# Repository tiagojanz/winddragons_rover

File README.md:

# WindDragons - Sistema de Telemetria e Controlo Náutico (Base & Rover)

Projeto de automação e telemetria para boias robóticas náuticas autónomas (**Rovers**) e estação de controlo com ecrã (**Base Station**), baseado na **arquitetura universal Dual ESP32-C6** (Master Lafvin LCD 1.47" + Coprocessador DevKitC-1).

---

## 🛰️ Arquitetura do Sistema (Dual ESP32-C6 em Ambos os Nós)

```
[ WindDragons Portal (Cloud) ]
        ▲
        │ HTTPS REST API (JSON)
        ▼
┌────────────────────────────────────────────────────────┐
│ BASE STATION (Dual ESP32-C6)                           │
│  - Master Lafvin: LCD 1.47" IPS, MicroSD, Web/WiFi,   │
│                   Joystick PS5 e Coordenador OTA Dual │
│         ▲                                              │
│         │ UART Inter-ESP (921600 baud)                │
│         ▼                                              │
│  - Coprocessador C6: Rádio LoRa SX1278 (433MHz)       │
└──────────────────────────┬─────────────────────────────┘
                           │
                           │ LoRa 433 MHz (Ra-02 / SX1278)
                           ▼
┌────────────────────────────────────────────────────────┐
│ ROVER (Boia Náutica - Dual ESP32-C6)                   │
│  - Master Lafvin: LCD 1.47" IPS, MicroSD, Web/WiFi,   │
│                   Joystick local e Coordenador OTA    │
│         ▲                                              │
│         │ UART Inter-ESP (921600 baud)                │
│         ▼                                              │
│  - Coprocessador C6: LoRa 433MHz, GPS LC29H, PWM     │
│    (Motor, Leme, Guincho, Trinco) e Sensores          │
└────────────────────────────────────────────────────────┘
```

---

## 🔌 Esquema de Barramentos e Conexões

O módulo **LoRa Ra-02 (SX1278 a 433MHz)** é ligado exclusivamente ao **Coprocessador ESP32-C6** (evitando conflito com o barramento SPI partilhado entre o LCD e o MicroSD do Lafvin):

### Módulo LoRa SX1278 (433MHz) — Coprocessador ESP32-C6 DevKitC
| Pino Ra-02 | Pino ESP32-C6 | Notas |
| :--- | :--- | :--- |
| **VCC** | `3.3V` | Barramento independente 3.3V_C6 |
| **GND** | `GND` | Terra comum de referência |
| **SCK** | `GPIO 5` | Hardware SPI SCLK |
| **MOSI**| `GPIO 7` | Hardware SPI MOSI |
| **MISO**| `GPIO 4` | Hardware SPI MISO |
| **NSS / CS** | `GPIO 6` | Hardware SPI CS do LoRa |
| **DIO0**| `GPIO 0` | Interrupção de receção de pacotes |

---

### Slot MicroSD (TF Card Onboard) — Em ambas as placas
O slot MicroSD está integrado diretamente na placa ESP32-C6-LCD-1.47 e partilha o barramento SPI com o ecrã ST7789:
| Função SD | Pino ESP32-C6 | Notas |
| :--- | :--- | :--- |
| **CS** | `IO4` | Chip Select do Cartão SD (Ativo LOW) |
| **MOSI** | `IO6` | Partilhado com LCD MOSI |
| **SCLK** | `IO7` | Partilhado com LCD SCLK |
| **MISO** | `IO5` | Linha de leitura MISO |

**Ficheiros suportados na raiz do cartão:**
- `/config.txt` — Ficheiro de configurações lido automaticamente no boot.
- `/waypoints.txt` — Ficheiro de coordenadas de navegação (lido no Rover).
- `/telemetry.csv` — Registo automático de telemetria (GPS, velocidade, rumo, bateria e estado do motor).

---

### Build 1: ROVER (A Boia)
| Componente | Pino do Módulo / Atuador | Pino ESP32-C6 | Função |
| :--- | :--- | :--- | :--- |
| **Motor (ESC)** | Sinal PWM | `IO0` | 50Hz PWM (1000µs a 2000µs, centro 1500µs) |
| **Servo do Leme** | Sinal PWM | `IO1` | 50Hz PWM (Ângulo de direção) |
| **Guincho Âncora** | Sinal PWM | `IO23` | Servo de rotação contínua (1500µs parado, <1500 desce, >1500 sobe) |
| **GPS Quectel LC29H** | TX do GPS | `IO19` | RX UART1 (115200 bps) |
| | RX do GPS | `IO18` | TX UART1 |
| | VCC / GND | `3.3V / GND` | Alimentação |
| **LED RGB Onboard** | Integrado | `IO8` | Estado: Verde (GPS OK), Azul (LoRa), Vermelho (Failsafe) |

---

### Build 2: BASE (Comando Remoto com Ecrã)
| Componente | Pino do Módulo | Pino ESP32-C6 | Função |
| :--- | :--- | :--- | :--- |
| **Joystick (4 vias)** | VCC | `3.3V` | Alimentação do joystick |
| | GND | `GND` | Terra |
| | VRx (Avanço/Recuo) | `IO0` | Entrada Analógica ADC1_CH0 (Aceleração) |
| | VRy (Direção) | `IO1` | Entrada Analógica ADC1_CH1 (Leme) |
| **Botões de Âncora** | Subir Âncora | `IO18` | Entrada Digital (Pull-up interno) |
| | Descer Âncora | `IO19` | Entrada Digital (Pull-up interno) |
| **Botão BOOT** | Onboard | `IO9` | Cicla páginas de ecrã (Comando -> Frota -> Rede) |
| **Ecrã LCD 1.47"** | Integrado ST7789 | `IO14, 15, 21, 22` | Dashboard multi-ecrã Landscape 320x172 (Comando, Frota de Rovers e Rede WiFi) |

---

## 🌐 Conectividade WiFi, Modo AP & Servidor Web

A Base Station inclui gestão inteligente de ligações WiFi e um Servidor Web HTTP responsivo:

### 1. Arranque Inteligente e Fallback para Modo AP:
- **No arranque**: a Base tenta ligar-se à rede marcada como **Padrão (Default)** ou às redes secundárias guardadas na memória NVS (timeout de 8s).
- **Se não houver ligação**: entra automaticamente em **Modo Ponto de Acesso (AP)**:
  - **SSID do AP**: `WindDragons-Base`
  - **Password**: `12345678`
  - **Endereço IP**: `http://192.168.4.1`
- **Ecrã LCD**: ao arrancar (e no menu através de `7. INFO REDE / IP`):
  - Se ligado a WiFi: apresenta o **endereço IP** atribuído (`http://192.168.x.x`), SSID e sinal RSSI.
  - Se em modo AP: apresenta o **SSID da Base**, a password e o endereço `http://192.168.4.1`.

### 2. Páginas do Servidor HTTP:
- **Em Modo AP**:
  - `/wifi`: Interface para procurar redes próximas (Scan WiFi), adicionar redes e marcar a rede de casa/porto como **Default**.
- **Em Modo WiFi (Cliente)**:
  - `/wifi`: Gestão de múltiplas redes guardadas, alteração da rede default, remoção e scanner de sinal.
  - `/gps`: Telemetria e coordenadas GPS do Rover ativo, rumo da proa, velocidade em nós e links diretos para Google Maps e OpenStreetMap.
  - `/battery`: Monitorização da bateria LiPo 4S (tensão do pack, média por célula, percentagem colorida e estado de saúde).
  - `/control`: Comando remoto da boia via rádio LoRa (acelerador do motor ESC com presets, leme, âncora, cremalheira, hold station e botão de paragem de emergência).

---

## 🚀 Como Compilar e Enviar o Firmware

Com o **PlatformIO** instalado:

### 1. Compilar e Enviar para o Rover:
O Rover possui dois módulos ESP32-C6:
- **Rover C6 (Slave):** Controla Rádio LoRa, GPS LC29H, ESC do Motor, Servos e Sensores.
- **Rover Lafvin (Master):** Controla o Ecrã LCD 1.47" ST7789, Leitor MicroSD e Joystick.

```bash
# Rover C6 (Slave - LoRa / GPS / Atuadores)
pio run -e rover_c6 -t upload
pio device monitor -e rover_c6

# Rover Lafvin (Master - LCD / MicroSD)
pio run -e rover_lafvin -t upload
pio device monitor -e rover_lafvin

# Ou gerar pacote unificado para atualização remota (OTA):
python3 scripts/bundle_firmware.py
```

### 2. Compilar e Enviar para a Base:
```bash
# Compilar e Enviar Base
pio run -e base -t upload

# Monitor Série (115200 baud)
pio device monitor -e base
```

---

## 📡 Integração com a API WindDragons

A cada 3 segundos, a Base agrupa os rovers ativos e envia um pedido `POST` para `https://winddragons.app/api/circuits/station/telemetry`:

```json
{
  "station_id": "BASE-ALCOCHETE-01",
  "rovers": [
    {
      "rover_code": "ROVER-01",
      "lat": 38.750508,
      "lng": -8.973995,
      "speed": 0.2,
      "heading": 185.0,
      "battery_pct": 92,
      "battery_voltage": 12.5,
      "motor_status": "holding_station",
      "anchor_status": "retracted",
      "anchor_depth_m": 0.0,
      "rssi": -65
    }
  ]
}
```

Caso o servidor responda com comandos pendentes (ex: `DROP_ANCHOR`, `RETRACT_ANCHOR`, `HOLD_STATION`), a Base coloca o comando na fila e transmite-o imediatamente via rádio LoRa para o rover visado!

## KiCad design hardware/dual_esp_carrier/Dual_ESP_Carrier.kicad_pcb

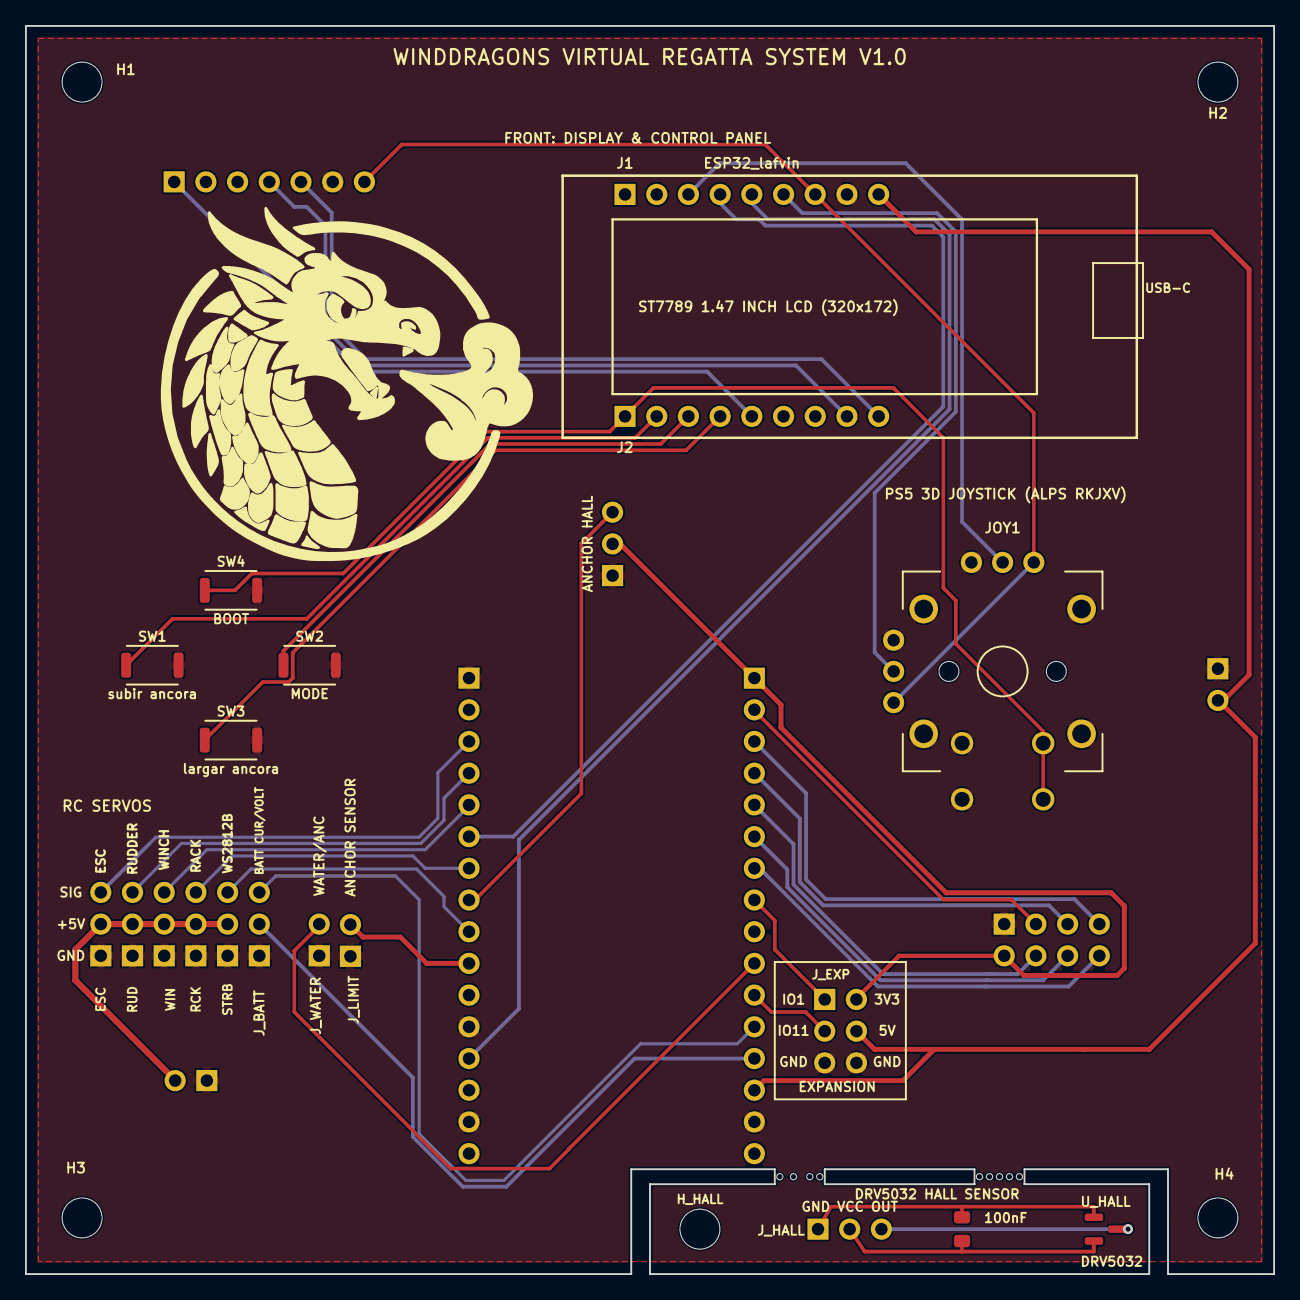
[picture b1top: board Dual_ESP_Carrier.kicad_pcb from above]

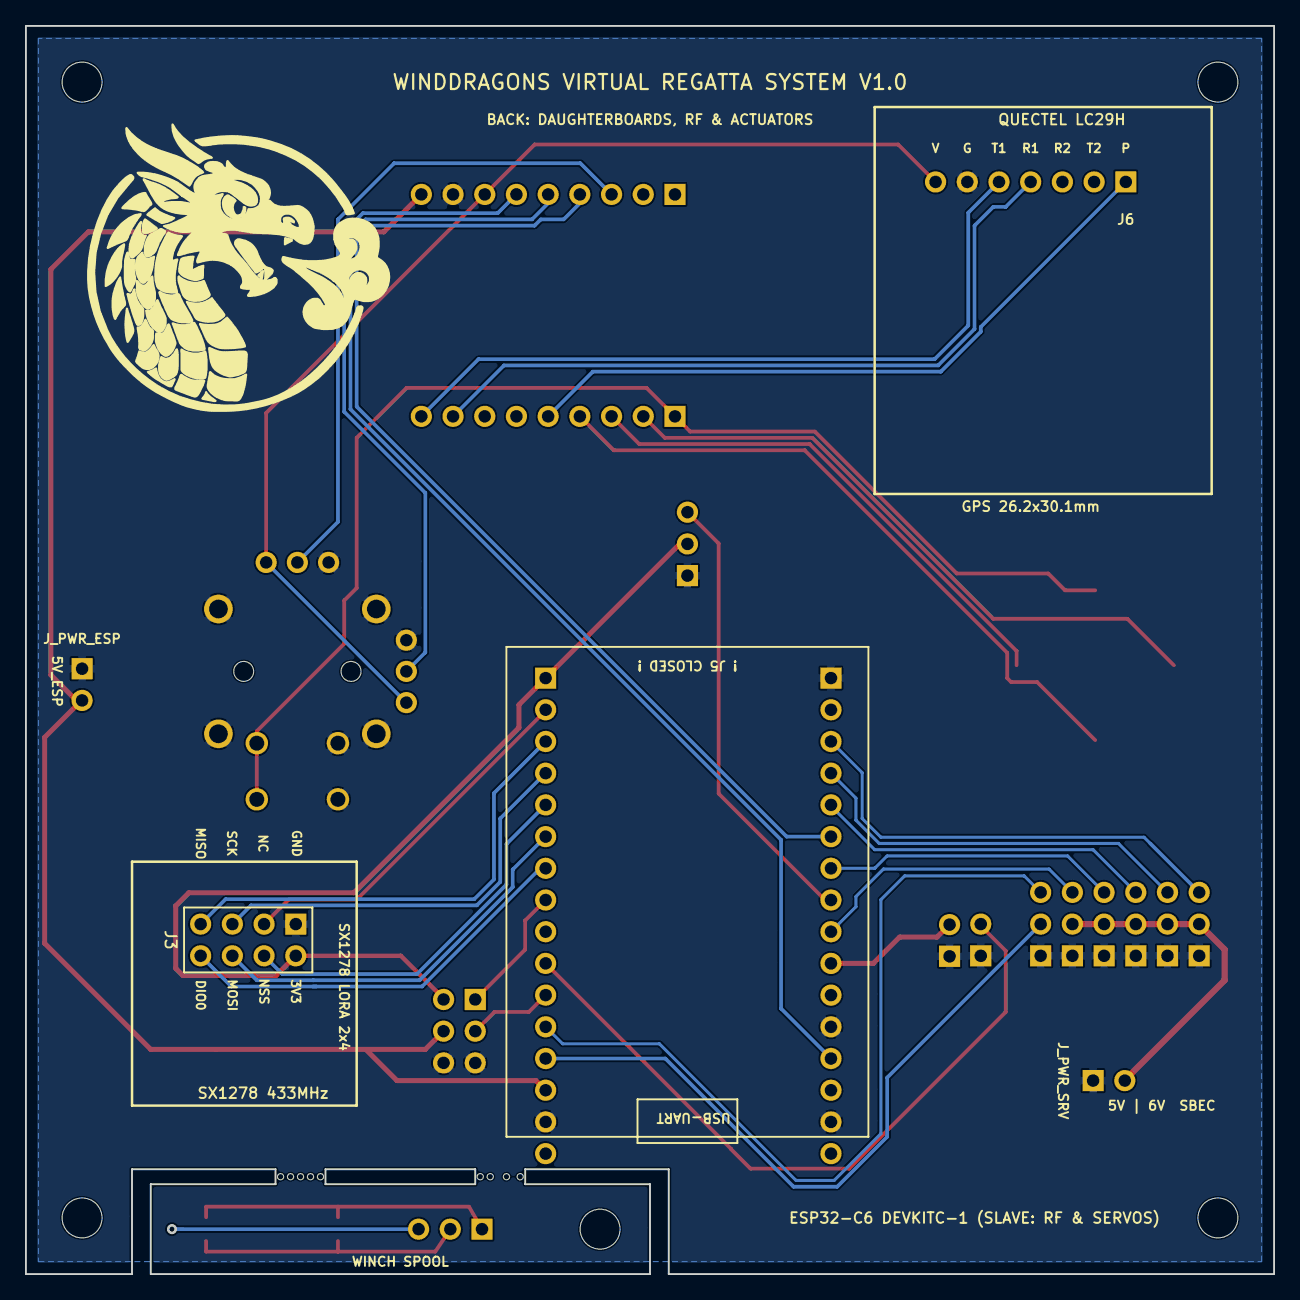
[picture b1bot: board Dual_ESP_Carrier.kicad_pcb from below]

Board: 2 copper layers, 100.0 x 100.0 mm, 40 parts (6 on the bottom side), 37 nets.

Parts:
C_HALL: 100nF; C_0805_2012Metric
ESC: ESC; PinHeader_1x03_P2.54mm_Vertical
H1, H2, H3, H4: MountingHole_3.2mm_M3
HALL: ANCHOR HALL; PinHeader_1x03_P2.54mm_Vertical
H_HALL: M3_MOUNT; MountingHole_3.2mm_M3
J1: ESP32_lafvin; PinHeader_1x09_P2.54mm_Horizontal
J2: ESP32_B_LANDSCAPE; PinHeader_1x09_P2.54mm_Horizontal
J3: SX1278_LORA_2x4; PinHeader_2x04_P2.54mm_Vertical
J6: GPS_LC29H_7PIN; PinHeader_1x07_P2.54mm_Horizontal
JOY1: PS5_JOYSTICK; Alps_RKJXV1224005
J_BATT: BATT CUR/VOLT; PinHeader_1x03_P2.54mm_Vertical
J_DK_L: PinHeader_1x16_P2.54mm_Vertical
J_DK_R: PinHeader_1x16_P2.54mm_Vertical
J_EXP: EXPANSION; PinHeader_2x03_P2.54mm_Vertical
J_HALL: GND_VCC_OUT; PinHeader_1x03_P2.54mm_Horizontal
J_LIMIT: ANCHOR SENSOR; PinHeader_1x02_P2.54mm_Vertical
J_PWR_ESP: 5V_ESP; PinHeader_1x02_P2.54mm_Vertical
J_PWR_SRV: 5V | 6V SBEC; PinHeader_1x02_P2.54mm_Vertical
J_WATER: WATER/ANC; PinHeader_1x02_P2.54mm_Vertical
RCK: RACK; PinHeader_1x03_P2.54mm_Vertical
RUD: RUDDER; PinHeader_1x03_P2.54mm_Vertical
STAMP: MountingHole_0.5mm
STAMP#2, STAMP#3, STAMP#4, STAMP#5, STAMP#6, STAMP#7, STAMP#8, STAMP#9: MountingHole_0.5mm
STRB: WS2812B; PinHeader_1x03_P2.54mm_Vertical
SW1: subir ancora; SKRKAEE020
SW2: MODE; SKRKAEE020
SW3: largar ancora; SKRKAEE020
SW4: BOOT; SKRKAEE020
U_HALL: DRV5032; SOT-23
WIN: WINCH; PinHeader_1x03_P2.54mm_Vertical

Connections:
/+3V3: J1.7, J6.7, JOY1.3, JOY1.6
/+3V3_C6: HALL.2, J3.2, J_DK_L.1, J_EXP.2
/+5V: J1.9, J_DK_L.14, J_EXP.4, J_PWR_ESP.2
/+5V_SERVO: ESC.2, J_PWR_SRV.2, RCK.2, RUD.2, STRB.2, WIN.2
/ANCHOR_HALL: HALL.3, J_DK_R.8
/ANCHOR_LIMIT: J_DK_R.10, J_LIMIT.2
/BATT_CURR: J_BATT.2, J_DK_L.13
/BATT_VOLT: J_BATT.3, J_DK_L.12
/EXP_IO1: J_DK_L.8, J_EXP.1
/EXP_IO11: J_DK_L.11, J_EXP.3
/GND: ESC.1, HALL.1, J1.8, J3.1, J6.6, JOY1.1, JOY1.4, JOY1.7, JOY1.8, JOY1.11, JOY1.12, JOY1.13, JOY1.14, J_BATT.1, J_DK_L.15, J_DK_R.1, J_DK_R.12, J_DK_R.15, J_EXP.5, J_EXP.6, J_LIMIT.1, J_PWR_ESP.1, J_PWR_SRV.1, J_WATER.1, RCK.1, RUD.1, STRB.1, SW1.2, SW2.2, SW3.2, SW4.2, WIN.1
/GPS_PPS: J2.5, J6.1
/GPS_RX: J2.8, J6.4
/GPS_TX: J2.9, J6.5
/HALL_GND: C_HALL.2, J_HALL.1, U_HALL.1
/HALL_OUT: J_HALL.3, U_HALL.3
/HALL_VCC: C_HALL.1, J_HALL.2, U_HALL.2
/INTER_RX_S2M: J1.5, J_DK_R.13
/INTER_TX_M2S: J1.4, J_DK_R.6
/IO9_BOOT: J2.1, JOY1.9, JOY1.10, SW4.1
/IO18_UP: J2.2, SW1.1
/IO19_MODE: J2.3, SW2.1
/IO20_DN: J2.4, SW3.1
/JOY_X: J1.3, JOY1.5
/JOY_Y: J1.6, JOY1.2
/LORA_DIO0: J3.8, J_DK_L.7
/LORA_MISO: J3.7, J_DK_L.3
/LORA_MOSI: J3.6, J_DK_L.6
/LORA_NSS: J3.4, J_DK_L.5
/LORA_RST: J3.3, J_DK_L.2
/LORA_SCK: J3.5, J_DK_L.4
/SERVO_ESC: ESC.3, J_DK_R.3
/SERVO_RACK: J_DK_R.7, RCK.3
/SERVO_RUDDER: J_DK_R.4, RUD.3
/SERVO_WINCH: J_DK_R.5, WIN.3
/STROBE_DIN: J_DK_R.9, STRB.3
/WATER_SENS: J_DK_L.10, J_WATER.2

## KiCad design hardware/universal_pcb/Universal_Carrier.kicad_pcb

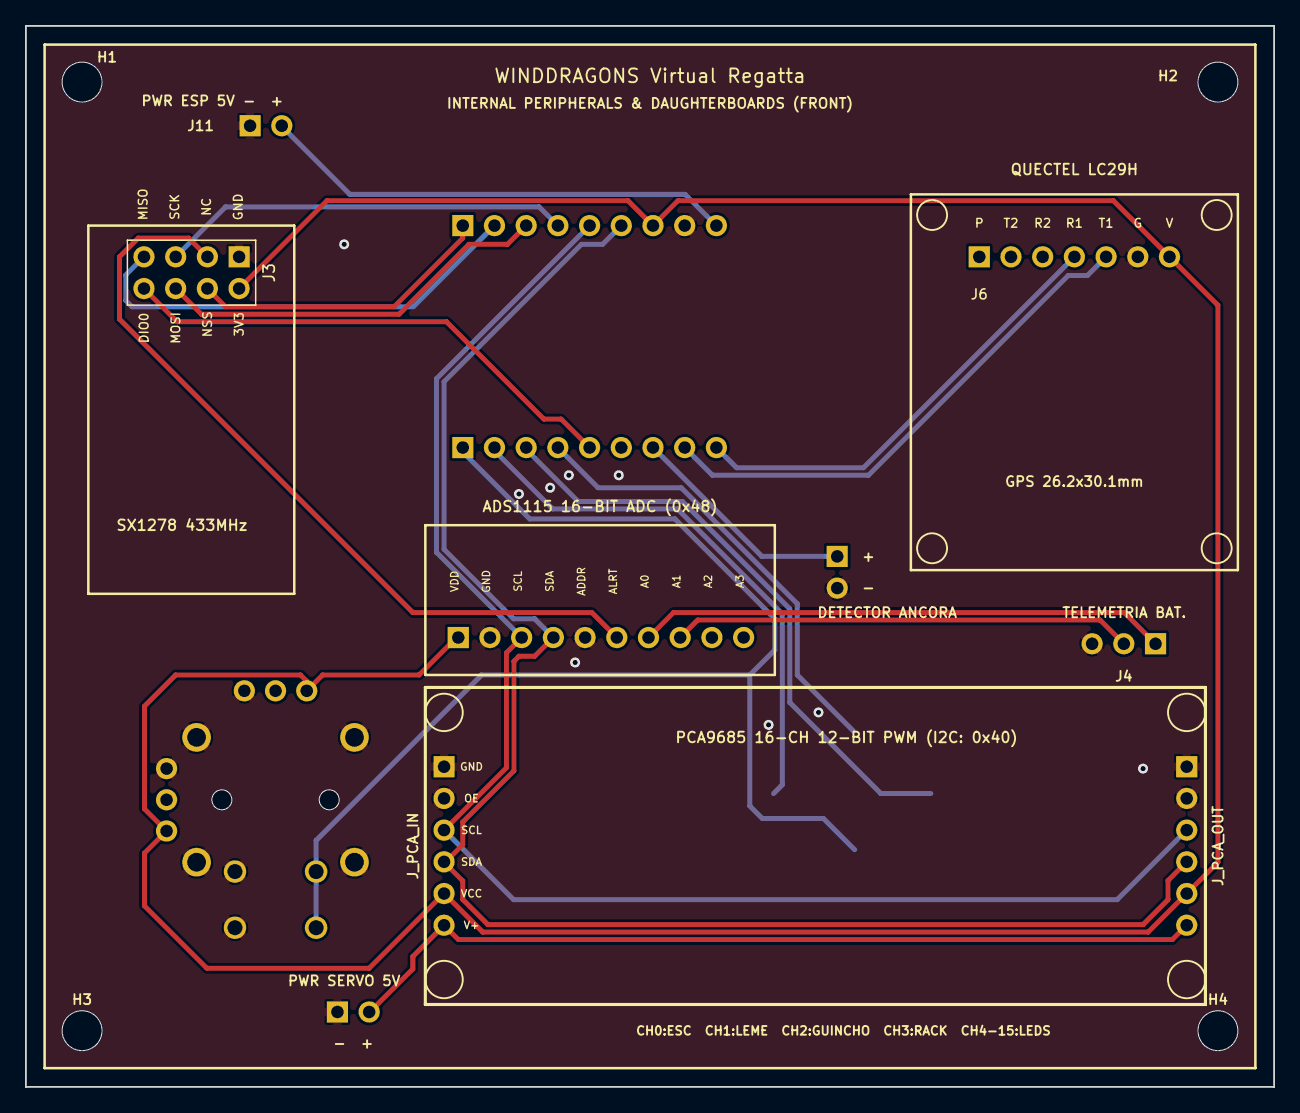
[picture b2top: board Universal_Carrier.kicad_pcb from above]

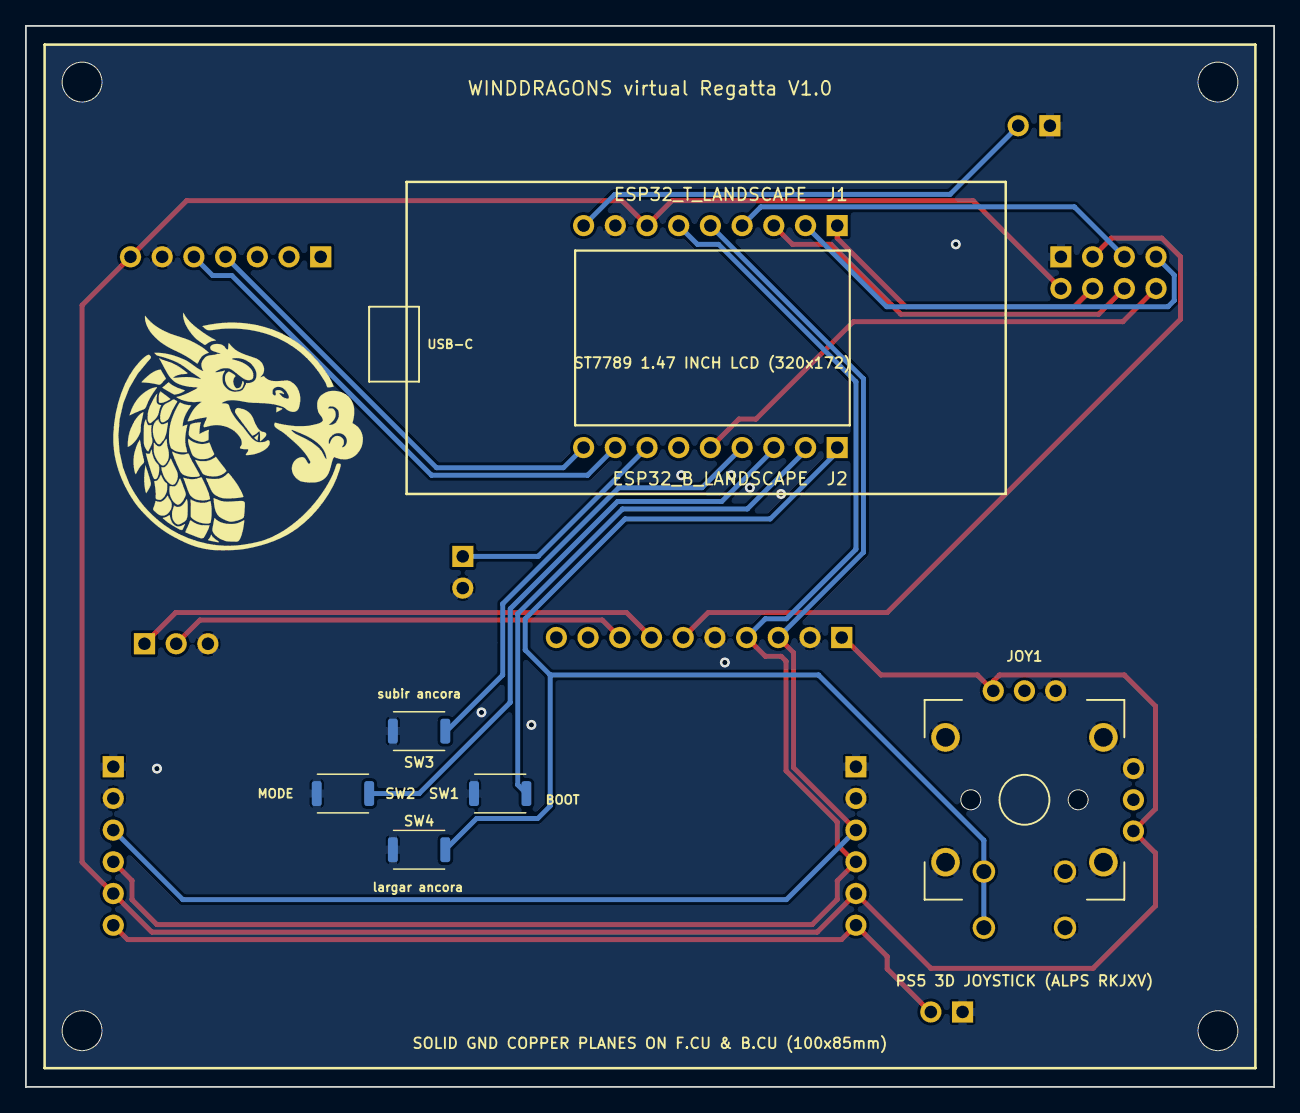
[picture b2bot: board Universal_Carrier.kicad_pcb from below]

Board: 2 copper layers, 100.0 x 85.0 mm, 21 parts (8 on the bottom side), 21 nets.

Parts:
H1, H2, H3, H4: MountingHole; MountingHole_3.2mm_M3
J1: ESP32_T_LANDSCAPE; PinHeader_1x09_P2.54mm_Horizontal
J2: ESP32_B_LANDSCAPE; PinHeader_1x09_P2.54mm_Horizontal
J3: SX1278_LORA_2x4; PinHeader_2x04_P2.54mm_Vertical
J4: BATT_APM; PinHeader_1x03_P2.54mm_Horizontal
J5: DETECTOR_ANCORA; PinHeader_1x02_P2.54mm_Vertical
J6: GPS_LC29H_7PIN; PinHeader_1x07_P2.54mm_Horizontal
J11: PWR_ESP_5V; PinHeader_1x02_P2.54mm_Horizontal
J12: PWR_SERVO_5V; PinHeader_1x02_P2.54mm_Horizontal
JOY1: PS5_JOYSTICK; Alps_RKJXV1224005
J_ADS: ADS1115_ADC; PinHeader_1x10_P2.54mm_Horizontal
J_PCA_IN: PCA9685_IN; PinHeader_1x06_P2.54mm_Vertical
J_PCA_OUT: PCA9685_OUT; PinHeader_1x06_P2.54mm_Vertical
LOGO1: WindDragons_Logo; WindDragons_Logo_20mm
SW1: subir ancora; SKRKAEE020
SW2: MODE; SKRKAEE020
SW3: largar ancora; SKRKAEE020
SW4: BOOT; SKRKAEE020

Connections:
/+3V3: J1.7, J3.2, J6.7, JOY1.3, JOY1.6, J_ADS.1, J_PCA_IN.5, J_PCA_OUT.5
/+5V: J1.9, J11.2
/+5V_SERVO: J12.2, J_PCA_IN.6, J_PCA_OUT.6
/BATT_CURR_APM: J4.2, J_ADS.8
/BATT_VOLT_APM: J4.1, J_ADS.7
/GND: J1.8, J3.1, J4.3, J5.2, J6.6, J11.1, J12.1, JOY1.1, JOY1.4, JOY1.7, JOY1.8, JOY1.11, JOY1.12, JOY1.13, JOY1.14, J_ADS.2, J_ADS.5, J_PCA_IN.1, J_PCA_IN.2, J_PCA_OUT.1, J_PCA_OUT.2, SW1.2, SW2.2, SW3.2, SW4.2
/I2C_SCL: J1.5, J_ADS.3, J_PCA_IN.3, J_PCA_OUT.3
/I2C_SDA: J1.6, J_ADS.4, J_PCA_IN.4, J_PCA_OUT.4
/IO2_SCK: J1.4, J3.5
/IO3_MOSI: J1.3, J3.6
/IO4_MISO: J1.2, J3.7
/IO5_NSS: J1.1, J3.4
/IO9_BOOT: J2.1, JOY1.9, JOY1.10, SW4.1
/IO13_ANCORA_DET: J2.7, J5.1
/IO16_GPS_RX: J2.8, J6.5
/IO17_GPS_TX: J2.9, J6.4
/IO18_UP: J2.2, SW1.1
/IO19_MODE: J2.3, SW2.1
/IO20_DN: J2.4, SW3.1
/IO23_LORA_DIO0: J2.5, J3.8
/NC: J3.3, J_ADS.6

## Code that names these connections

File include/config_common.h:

#pragma once

#include <Arduino.h>

// ==========================================
// PIN DEFINITIONS - LAFVIN ESP32-C6 1.47" LCD
// ==========================================

// --- Onboard LCD (ST7789 172x320 - internal hardware SPI) ---
#define PIN_LCD_MOSI 6
#define PIN_LCD_SCLK 7
#define PIN_LCD_CS 14
#define PIN_LCD_DC 15
#define PIN_LCD_RST 21
#define PIN_LCD_BL 22
#define LCD_WIDTH 172
#define LCD_HEIGHT 320
#define DISPLAY_ROTATION 1 // 1 = Landscape (320x172), 3 = Landscape 180°
#define SCREEN_W 320
#define SCREEN_H 172

// --- Onboard MicroSD / TF Card (Shares SPI bus with ST7789 LCD) ---
#define PIN_SD_CS                                                              \
  4 // MicroSD Chip Select (Active LOW, Top Header Pin 2 / onboard TF)
#define PIN_SD_MOSI PIN_LCD_MOSI // GPIO 6 (Shared Hardware SPI MOSI)
#define PIN_SD_SCLK PIN_LCD_SCLK // GPIO 7 (Shared Hardware SPI SCLK)
#define PIN_SD_MISO 5            // GPIO 5 (Shared Hardware SPI MISO)

// --- Onboard Peripherals ---
#define PIN_RGB_LED 8 // WS2812 NeoPixel
#define PIN_BTN_BOOT                                                           \
  9 // Hardware BOOT button on ESP32-C6 & SW4 (BOOT) on Carrier PCB
#define PIN_BTN_SW1 18 // Navigation SW1 Left (UP) on Carrier PCB

// --- LoRa SX1278 (Ra-02 433MHz) on Dedicated Header SPI ---
// NOTA CRÍTICA ESP32-C6: O ESP32-C6 tem apenas UM barramento SPI de utilizador
// (FSPI). Além disso, GPIO 4 e 5 são partilhados com o leitor MicroSD TF
// onboard. Definir ENABLE_LORA como 1 apenas quando o módulo LoRa estiver
// fisicamente ligado e a ser usado.
#ifndef ENABLE_LORA
#define ENABLE_LORA 1
#endif

// Top Header: Pin 4 (SCK=2), Pin 3 (MOSI=3)
// Bottom Header: Pin 3 (MISO=19), Pin 4 (NSS=20), Pin 5 (DIO0=23)
#define PIN_LORA_SCK 2  // SPI SCLK (Top Header Pin 4)
#define PIN_LORA_MOSI 3 // SPI MOSI (Top Header Pin 3)
#define PIN_LORA_MISO                                                          \
  19 // SPI MISO (Bottom Header Pin 3 / GPIO 19 - sem conflito com MicroSD)
#define PIN_LORA_NSS                                                           \
  20 // CS/NSS for LoRa (Bottom Header Pin 4 / GPIO 20 - sem conflito com
     // MicroSD)
#define PIN_LORA_DIO0                                                          \
  23 // LoRa DIO0 IRQ (Bottom Header Pin 5 / GPIO 23 - sem conflito com USB)
#define PIN_LORA_RST -1 // Not connected / internal pullup

// LoRa RF Settings (433MHz Band)
#define LORA_FREQUENCY 433.0 // MHz
#define LORA_BANDWIDTH 250.0 // kHz (fast throughput for multi-rover polling)
#define LORA_SPREAD_FACTOR 7 // SF7 (low latency, high data rate)
#define LORA_CODING_RATE 5   // 4/5
#define LORA_SYNC_WORD 0x12  // Private network sync word
#define LORA_OUTPUT_POWER 17 // dBm (up to 20 dBm supported)
#define LORA_PREAMBLE_LEN 8

// --- I2C Expansion Bus (ESP32-C6 IO0 & IO1) ---
#define PIN_I2C_SDA 0 // ESP32 GPIO 0 (SDA)
#define PIN_I2C_SCL 1 // ESP32 GPIO 1 (SCL)

// --- Ilha de Expansão J_EXP na PCB C6 (Bússola GY-BNO055 9-DOF) ---
// J_EXP Pino 1 (IO1)  -> GPIO 1  (I2C SDA)
// J_EXP Pino 2 (3V3)  -> +3.3V
// J_EXP Pino 3 (IO11) -> GPIO 11 (I2C SCL)
// J_EXP Pino 5/6 (GND)-> GND
#define PIN_C6_EXP_SDA 1
#define PIN_C6_EXP_SCL 11
#define BNO055_I2C_ADDR_A 0x28
#define BNO055_I2C_ADDR_B 0x29

// ==========================================
// INTER-ESP UART DEFINITIONS (Lafvin Master <-> ESP32-C6 Slave)
// ==========================================
// Testado e 100% validado em bancada a 115200 bps (0% perdas, RTT ~36ms em
// cadeia) Amarelo: C6 TX (GPIO 13) -> Lafvin RX (GPIO 1 / Pad 5) Verde: Lafvin
// TX (GPIO 2 / Pad 4) -> C6 RX (GPIO 22) Preto:   GND Comum
#define PIN_INTER_ESP_LAFVIN_TX                                                \
  2 // Lafvin Header J1 Pad 4 (Serigrafia 2 / GPIO 2)
#define PIN_INTER_ESP_LAFVIN_RX                                                \
  1                            // Lafvin Header J1 Pad 5 (Serigrafia 1 / GPIO 1)
#define PIN_INTER_ESP_C6_TX 13 // C6 DevKitC Header J3 Pin 13 (GPIO 13)
#define PIN_INTER_ESP_C6_RX 22 // C6 DevKitC Header J3 Pin 6 (GPIO 22)
#define INTER_ESP_BAUDRATE 115200

// ==========================================
// C6 DEVKITC ROVER PIN DEFINITIONS (COPROCESSADOR)
// ==========================================
// LoRa SX1278 (Ra-02 433MHz no barramento de hardware FSPI do DevKitC)
#define PIN_C6_LORA_NSS 6  // GPIO 6
#define PIN_C6_LORA_SCK 5  // GPIO 5
#define PIN_C6_LORA_MOSI 7 // GPIO 7
#define PIN_C6_LORA_MISO 4 // GPIO 4
#define PIN_C6_LORA_DIO0 0 // GPIO 0
#define PIN_C6_LORA_RST -1 // Sem reset externo

// Power Module (LiPo 6S) via ADC interno do ESP32-C6
#define PIN_C6_ADC_VOLT 2 // GPIO 2
#define PIN_C6_ADC_CURR 3 // GPIO 3
#define BATT_VOLT_DIVIDER 10.803f
#define BATT_AMPS_PER_VOLT 27.32f
#define BATT_CURR_OFFSET_MV 6.5f

// Sensor de Água
#define PIN_C6_WATER_SENS 15 // GPIO 15 (Entrada Analógica)

// GPS Quectel LC29H (UART Hardware)
#define PIN_LAFVIN_GPS_RX 16 // Lafvin Header J2 Pad 8 (Serigrafia RX / GPIO 16)
#define PIN_LAFVIN_GPS_TX 17 // Lafvin Header J2 Pad 9 (Serigrafia TX / GPIO 17)
#define PIN_C6_GPS_RX 16     // DevKitC RX (GPIO 16)
#define PIN_C6_GPS_TX 17     // DevKitC TX (GPIO 17)
#define GPS_BAUDRATE 115200

// Atuadores / Servos (Sinais PWM Diretos)
// NOTA PCB: O conector WIN da PCB liga ao Pino 5 do J_DK_R (GPIO 23 no ESP32-C6
// DevKitC)
#define PIN_C6_WINCH 23 // GPIO 23 - Conector WIN na PCB (DevKitC J3 Pin 5)
#define PIN_C6_WINCH_ALT                                                       \
  -1 // Desativado: GPIO 19 dedicado a LEDs WS2812B Strobe
#define PIN_C6_SERVO_RACK 21 // GPIO 21 - Conector RCK na PCB (DevKitC J3 Pin 7)
#define PIN_C6_SERVO_RUD 15  // GPIO 15 - Conector RUD na PCB (DevKitC J3 Pin 4)
#define PIN_C6_MOTOR_ESC 17  // GPIO 17 - Conector ESC na PCB (DevKitC J3 Pin 3)

// Fim de Curso da Âncora (Microswitch topo)
#define PIN_ANCHOR_DETECTOR                                                    \
  18 // GPIO 18 no DevKitC (INPUT_PULLUP, fecha ao GND no topo)

// Sensor de Efeito Hall do Tambor da Âncora (DRV5032)
#define PIN_ANCHOR_HALL                                                        \
  20 // GPIO 20 no DevKitC (INPUT_PULLUP, contador de voltas do tambor)

// Fita / Módulo de LEDs WS2812B Strobe Náutico
#define PIN_STROBE_LEDS 19 // GPIO 19 no DevKitC (Linha de dados DIN WS2812B)
#define NUM_STROBE_LEDS 8  // Quantidade padrão de LEDs na fita/anel

// Aliases e compatibilidade
#define PIN_GPS_RX PIN_C6_GPS_RX
#define PIN_GPS_TX PIN_C6_GPS_TX
#define ADS1115_I2C_ADDR 0x48
#define ADS_CH_BATT_VOLT 0
#define ADS_CH_BATT_CURR 1
#define ADS_CH_WATER_SENS 2
#define ADS_CH_AUX 3

// PCA9685 I2C Channels (Opcional / Compatibilidade)
#define PCA9685_I2C_ADDR 0x40
#define PCA_CH_MOTOR 0  // Main propulsion ESC
#define PCA_CH_RUDDER 1 // Rudder servo
#define PCA_CH_WINCH 2  // Anchor winch servo
#define PCA_CH_RACK 3   // Anchor rack/clutch servo

// Posições padrão da cremalheira (configuráveis em NVS / SD)
#define RACK_POS_ENGAGED 0   // Ângulo padrão de encosto (cremalheira engatada / travada)
#define RACK_POS_RELEASED                                                      \
  90 // Ângulo padrão livre (cremalheira levantada para queda da âncora por gravidade)
#define RACK_SERVO_INVERTED_DEFAULT                                            \
  true // Direção do servo da cremalheira invertida por defeito

// Limites de pulso PWM
#define PWM_PULSE_MIN 1000
#define PWM_PULSE_MID 1500
#define PWM_PULSE_MAX 2000

// ==========================================
// BASE PIN DEFINITIONS
// ==========================================
// 4-pin Joystick connector on Top Header J1 (Pads 3 e 6)
#define PIN_JOYSTICK_X 3 // ADC1_CH3 (Lafvin J1 Pad 3 / Serigrafia 3)
#define PIN_JOYSTICK_Y 0 // ADC1_CH0 (Lafvin J1 Pad 6 / Serigrafia 0)
#define PIN_JOYSTICK_SW                                                        \
  -1 // Desativado no joystick: GPIO 9 e o botao BOOT com interrupcao dedicada
     // para mudar de pagina

// Physical buttons on Base (Bottom Header)
#define PIN_BTN_ANCHOR_UP                                                      \
  18 // Button to hoist anchor / UP (SW1 Left - Bottom Header Pin 2 / IO18)
#define PIN_BTN_ANCHOR_DOWN                                                    \
  20 // Button to drop anchor / DOWN (SW3 Bottom - Bottom Header Pin 4 / IO20)
#define PIN_BTN_MODE                                                           \
  19 // Button for mode toggle / MODE (SW2 Right - Bottom Header Pin 3 / IO19)

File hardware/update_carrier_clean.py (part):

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        '			(symbol "Joystick_PS5_Thumbstick_1_1"',
        '				(rectangle (start -10.16 12.70) (end 10.16 -15.24) (stroke (width 0.254) (type default)) (fill (type background)))',
        '				(pin passive line (at -13.97 10.16 0) (length 3.81) (name "Y_GND" (effects (font (size 0.9 0.9)))) (number "1" (effects (font (size 0.9 0.9)))))',
        '				(pin passive line (at -13.97 7.62 0) (length 3.81) (name "JOY_Y" (effects (font (size 0.9 0.9)))) (number "2" (effects (font (size 0.9 0.9)))))',
        '				(pin passive line (at -13.97 5.08 0) (length 3.81) (name "Y_3V3" (effects (font (size 0.9 0.9)))) (number "3" (effects (font (size 0.9 0.9)))))',
        '				(pin passive line (at -13.97 0.00 0) (length 3.81) (name "X_GND" (effects (font (size 0.9 0.9)))) (number "4" (effects (font (size 0.9 0.9)))))',
        '				(pin passive line (at -13.97 -2.54 0) (length 3.81) (name "JOY_X" (effects (font (size 0.9 0.9)))) (number "5" (effects (font (size 0.9 0.9)))))',
        '				(pin passive line (at -13.97 -5.08 0) (length 3.81) (name "X_3V3" (effects (font (size 0.9 0.9)))) (number "6" (effects (font (size 0.9 0.9)))))',
        '				(pin passive line (at 13.97 10.16 180) (length 3.81) (name "SW_GND1" (effects (font (size 0.9 0.9)))) (number "7" (effects (font (size 0.9 0.9)))))',
        '				(pin passive line (at 13.97 7.62 180) (length 3.81) (name "SW_GND2" (effects (font (size 0.9 0.9)))) (number "8" (effects (font (size 0.9 0.9)))))',
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        sch_lines.append('	)')
        left_pins = [
            (10.16, "GND"),     # Pin 1: Y_GND
            (7.62, "JOY_Y"),    # Pin 2: JOY_Y
            (5.08, "+3V3"),     # Pin 3: Y_3V3
            (0.00, "GND"),      # Pin 4: X_GND
            (-2.54, "JOY_X"),   # Pin 5: JOY_X
            (-5.08, "+3V3"),    # Pin 6: X_3V3
        ]
        for py, lbl in left_pins:
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        right_pins = [
            (10.16, "GND"),      # Pin 7: SW_GND1
            (7.62, "GND"),       # Pin 8: SW_GND2
            (5.08, "IO9_BOOT"),  # Pin 9: SW_SIG1
            (2.54, "IO9_BOOT"),  # Pin 10: SW_SIG2
            (-2.54, "GND"),      # Pin 11: SH1
            (-5.08, "GND"),      # Pin 12: SH2
            (-7.62, "GND"),      # Pin 13: SH3
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
    # BLOCK 3: GNSS / GPS LC29H
    add_block("3. GNSS / GPS NAVIGATION (LC29H)", "UART Port (GP16 RX, GP17 TX) + 3V3", 152.40, 91.44, 264.16, 172.72)
    gps_labels = ["IO15", "GPS_TX2", "GPS_RX2", "IO17_GPS_TX", "IO16_GPS_RX", "GND", "+3V3"]
    place_conn_1row("Connector_Generic:Conn_01x07", "J6", "GPS_LC29H_7PIN", "Connector_PinHeader_2.54mm:PinHeader_1x07_P2.54mm_Horizontal", 218.44, 137.16, gps_labels)

    # BLOCK 4: Dual Joystick Interface & Pre-Launch Test Jumpers
    add_block("4. DUAL JOYSTICK INTERFACE", "Onboard PS5 Thumbstick (JOY1), RBL Jumpers (JP_RBL) & External Battery Port (J4)", 274.32, 20.32, 406.40, 114.30)
    place_joystick("JOY1", "PS5_JOYSTICK", "PS5_joystick:Alps_RKJXV1224005", 314.96, 66.04)
    rbl_labels = ["JOY_X", "IO0_ADC", "JOY_Y", "IO1_ADC"]
    place_conn_1row("Connector_Generic:Conn_01x04", "JP_RBL", "REMOVE_BEFORE_LAUNCH", "Connector_PinHeader_2.54mm:PinHeader_1x04_P2.54mm_Vertical", 347.98, 66.04, rbl_labels)
    apm_labels = ["IO0_ADC", "IO1_ADC", "GND"]
    place_conn_1row("Connector_Generic:Conn_01x03", "J4", "BATT_APM", "Connector_PinHeader_2.54mm:PinHeader_1x03_P2.54mm_Horizontal", 381.00, 64.77, apm_labels)
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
